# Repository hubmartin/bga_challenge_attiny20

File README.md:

# BGA Challenge

I wanted to improve my assembly and "cutting-edge" PCB pool technical size limits so I've designed this board in KiCAD. It's just 20 x 15 mm PCB.

Board was made with Aisler. Here is the [sharing link](https://aisler.net/p/JWEQJIAC) if you would like to manufacture PCB and stencil.

More info and pictures in these tweets:
- https://twitter.com/hubmartin/status/1266421947304476685
- https://twitter.com/hubmartin/status/1251945517552144384

# ATTiny20 programming

This board is using 6 pin programmer. ATTiny20 is using TPI programming (instead of ISP) where MOSI pin is bi-directional. You can use [USBasp  programmer by Thomas Fischl](https://www.fischl.de/usbasp/), make sure you have the latest version of firmware with TPI support `usbasp.2011-05-28`. I've read that chinese clones use older firmwares (11 years).

You can also use Arduino to program chip. [Bitluni has a great video about it.](https://www.youtube.com/watch?v=AL9vK_xMt4E)

# Example code

The example code is just blinking to test that you soldered everything right. The power-switch is not controlled yet, as I did not managed to solder this 2x2 BGA correctly yet.

You compile firmware with `build.sh` and flash it with `flash.sh`. Other scripts are for ATtiny204 but that's a different project.

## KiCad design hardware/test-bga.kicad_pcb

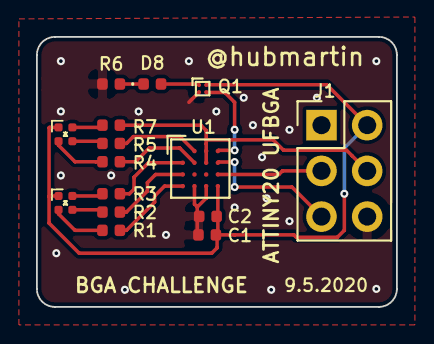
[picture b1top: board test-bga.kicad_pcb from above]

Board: 2 copper layers, 20.0 x 15.0 mm, 15 parts (0 on the bottom side), 19 nets.

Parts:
C1: 100nF; C_0402_1005Metric
C2: 1uF; C_0402_1005Metric
D1, D7: LED_ARGB; LED_TRI_1010
D8: LED; LED_0402_1005Metric
J1: Conn_02x03_Odd_Even; PinHeader_2x03_P2.54mm_Vertical
Q1: TPS22914; BGA-4_0.7x0.7mm_Layout2x2_P0.4mm
R1, R2, R3, R4, R5, R6, R7: 1k; R_0402_1005Metric
U1: ATtiny20-CCU; UFBGA-15_3.0x3.0mm_Layout4x4_P0.65mm

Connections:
/PWR_SW: Q1.B2, U1.A4
/RESET: J1.5, U1.B4
/TPICLK: J1.3, U1.C4
/TPIDATA: J1.4, R7.1, U1.A3, U1.B3
GND: C1.2, C2.2, J1.6, Q1.B1, R6.2, U1.D2, U1.D3
unnamed: D1.2, R7.2
unnamed: D1.3, R5.2
unnamed: D1.4, R4.2
unnamed: D7.2, R3.2
unnamed: D7.3, R2.2
unnamed: D7.4, R1.2
unnamed: D8.1, R6.1
unnamed: D8.2, Q1.A1
unnamed: R1.1, U1.D1
unnamed: R2.1, U1.C1
unnamed: R3.1, U1.B1
unnamed: R4.1, U1.B2
unnamed: R5.1, U1.A2
VCC: C1.1, C2.1, D1.1, D7.1, J1.2, Q1.A2, U1.D4

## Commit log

2020-06-03 Readme
